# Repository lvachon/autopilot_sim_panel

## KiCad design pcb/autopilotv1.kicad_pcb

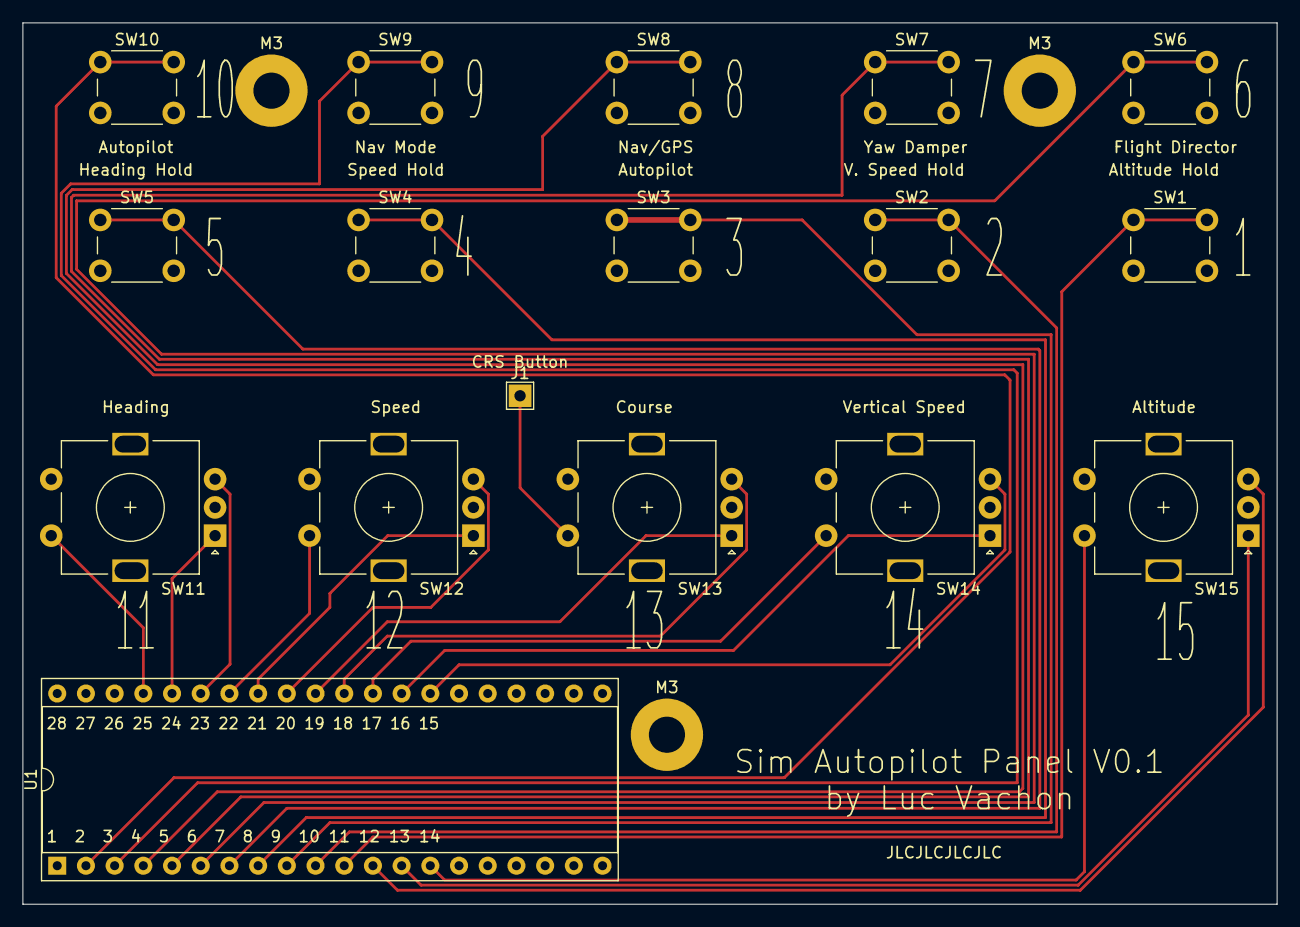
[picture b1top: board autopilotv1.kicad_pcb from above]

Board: 2 copper layers, 111.0 x 78.0 mm, 20 parts (0 on the bottom side), 26 nets.

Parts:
J1: Conn_01x01; TestPoint_THTPad_2.0x2.0mm_Drill1.0mm
M3, M3#2, M3#3: MountingHole_3.2mm_M3_Pad
SW1, SW2, SW3, SW4, SW5, SW6, SW7, SW8, SW9, SW10: My2pin_SW_MEC_5G; SW_PUSH_6mm
SW11, SW12, SW13, SW14, SW15: Rotary_Encoder_Switch; RotaryEncoder_Alps_EC11E-Switch_Vertical_H20mm
U1: Teensy3_2; DIP-40_W15.24mm_Socket

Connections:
GND: SW1.2, SW2.2, SW3.2, SW4.2, SW5.2, SW6.2, SW7.2, SW8.2, SW9.2, SW10.2, SW11.C, SW11.S1, SW12.C, SW12.S1, SW13.C, SW13.S1, SW14.C, SW14.S1, SW15.C, SW15.S1, U1.1, U1.39
unnamed: J1.1, SW13.S2
unnamed: SW1.1, U1.11
unnamed: SW2.1, U1.10
unnamed: SW3.1, U1.9
unnamed: SW4.1, U1.8
unnamed: SW5.1, U1.7
unnamed: SW6.1, U1.6
unnamed: SW7.1, U1.5
unnamed: SW8.1, U1.4
unnamed: SW9.1, U1.3
unnamed: SW10.1, U1.2
unnamed: SW11.A, U1.36
unnamed: SW11.B, U1.35
unnamed: SW11.S2, U1.37
unnamed: SW12.A, U1.33
unnamed: SW12.B, U1.32
unnamed: SW12.S2, U1.34
unnamed: SW13.A, U1.31
unnamed: SW13.B, U1.30
unnamed: SW14.A, U1.28
unnamed: SW14.B, U1.27
unnamed: SW14.S2, U1.29
unnamed: SW15.A, U1.13
unnamed: SW15.B, U1.12
unnamed: SW15.S2, U1.14

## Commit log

2020-08-24 Thoughts before starting
2020-08-24 Initial layout and button role call sketches
2020-08-30 Schematic, PCB, and Gerber files. I haven't even gotten all of the parts in yet, so who knows if this will stay.
2020-09-07 It works!
2020-09-07 cleanup
2020-09-07 more cleanup and some pics
2020-09-08 Better debounce for the encoders
2020-09-12 Better debouncing on the rotary encoders
2020-09-28 Adjustments to case top and button caps
